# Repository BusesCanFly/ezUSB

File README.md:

# ezUSB
Simple eUSB adapter

## What is this?
A very simple USB adapter for eUSB modules (the industrial version of a USB thumb drive)

There are several adapters online but they're either [no longer sold](https://www.amazon.com/U-Reach-eUSB-converter-2-0mm-5-PACK/dp/B016PD8TIA), [expensive](https://www.cmizapper.com/products/eusb.html), or [bulky](https://www.aliexpress.us/item/3256803756389704.html). 

You can very easily cut a USB cable, wire up a multipurpose USB breakout, but I wanted a simple, easy eUSB adapter - so, now we have ezUSB! :)

## Modes

ezUSB was designed to be as easy as possible - you can solder in a USB-C receptacle and the optional CC line resistors, leaving the header row avaliable as a USB breakout! Alternatively, simply solder on an [Adafruit USB-C breakout](https://www.adafruit.com/product/4090).

#### s/o Team Dumpsterfire <3

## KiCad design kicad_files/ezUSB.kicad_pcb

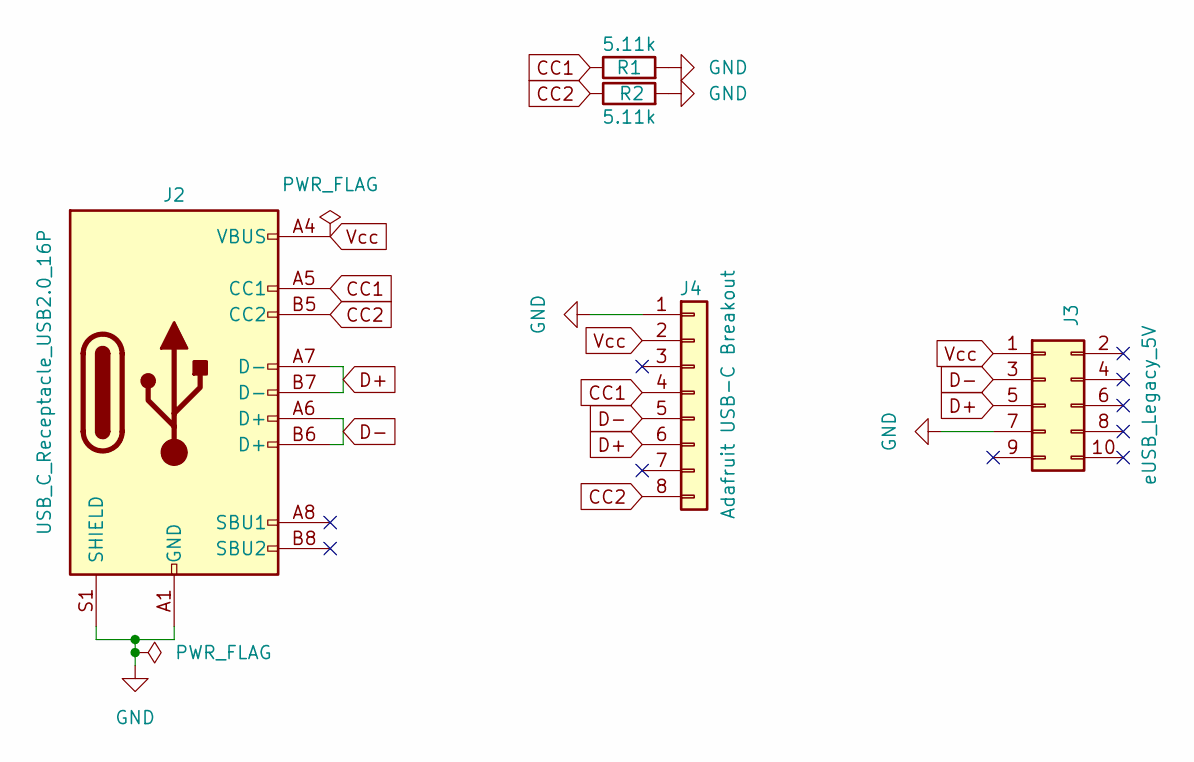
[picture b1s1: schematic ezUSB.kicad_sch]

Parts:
J2: USB_C_Receptacle_USB2.0_16P; USB_C_Receptacle_XKB_U262-16XN-4BVC11
J3: eUSB_Legacy_5V; PinHeader_2x05_P2.54mm_Vertical
J4: Adafruit USB-C Breakout; PinHeader_1x08_P2.54mm_Vertical
R1, R2: 5.11k; R_0603_1608Metric_Pad0.98x0.95mm_HandSolder

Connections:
CC1: J2.A5 (CC1), J4.4, R1.1
CC2: J2.B5 (CC2), J4.8, R2.1
D+: J2.A7 (D-), J2.B7 (D-), J3.5, J4.6
D-: J2.A6 (D+), J2.B6 (D+), J3.3, J4.5
GND: J2.A1 (GND), J2.A12 (GND), J2.B1 (GND), J2.B12 (GND), J2.S1 (SHIELD), J3.7, J4.1, R1.2, R2.2
Vcc: J2.A4 (VBUS), J2.A9 (VBUS), J2.B4 (VBUS), J2.B9 (VBUS), J3.1, J4.2

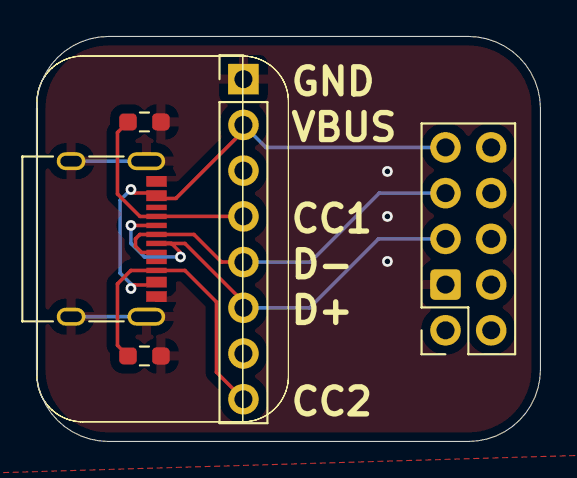
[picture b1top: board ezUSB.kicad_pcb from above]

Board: 2 copper layers, 28.0 x 22.5 mm, 5 parts (0 on the bottom side), 6 nets.

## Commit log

2024-03-07 added board files
2024-03-07 writeup
